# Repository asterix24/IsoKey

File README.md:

# IsoKey
Isometrical keyboard keys

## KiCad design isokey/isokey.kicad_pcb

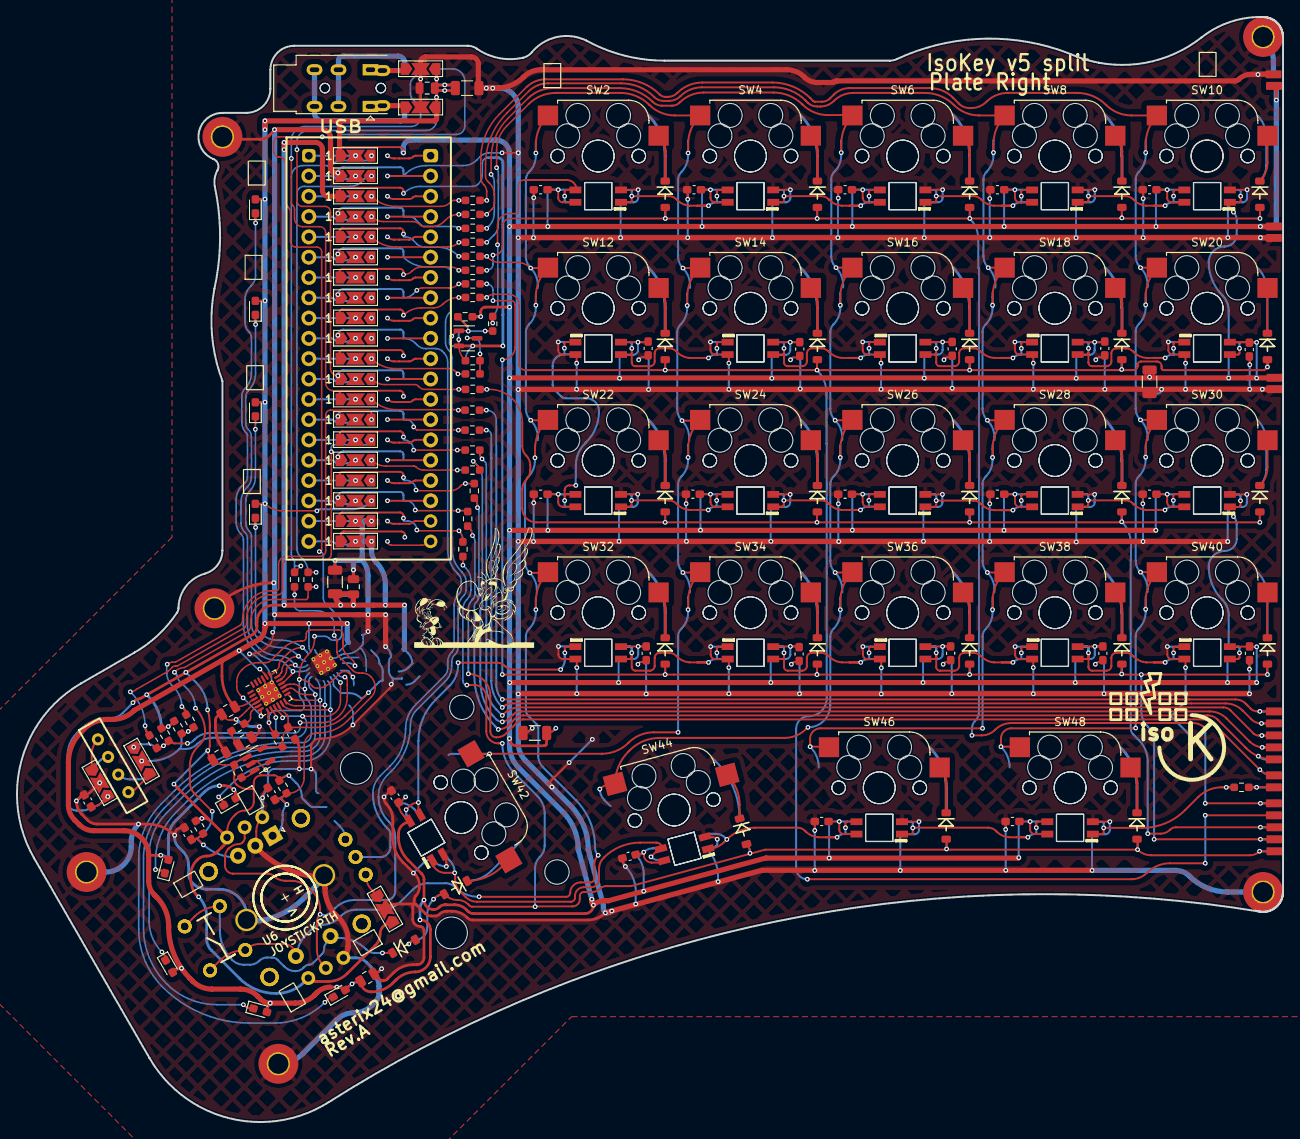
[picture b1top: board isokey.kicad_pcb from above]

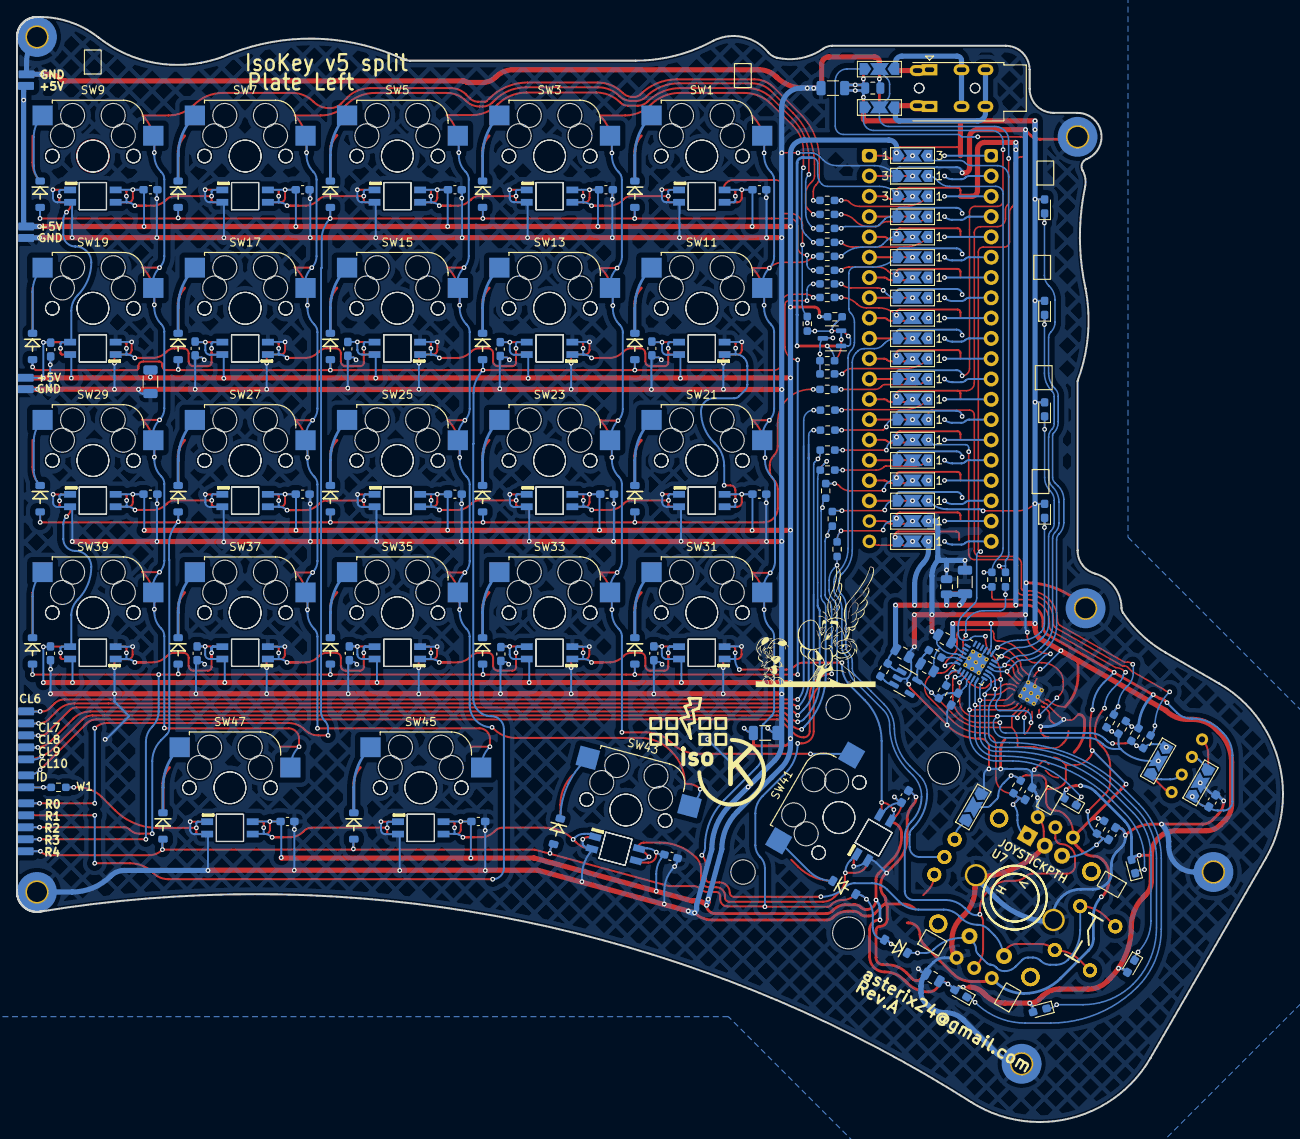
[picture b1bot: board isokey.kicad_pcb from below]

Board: 2 copper layers, 158.4 x 138.3 mm, 392 parts (182 on the bottom side), 200 nets.

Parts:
C1, C3, C10, C11, C38, C64, C71, C73, C74, C75, C87, C89: 1uF; C_0805_2012Metric
C2, C4, C5, C6, C63, C65, C66, C67: 10uF; C_1206_3216Metric
C7, C8, C9, C14, C15, C16, C17, C18, C19, C20, C21, C22, C23, C24, C25, C26, C27, C28, C29, C30, C31, C32, C33, C34, C35, C36, C37, C39, C40, C41, C42, C43, C44, C45, C46, C47, C48, C49, C50, C51, C52, C53, C54, C55, C56, C57, C58, C59, C60, C61, C62, C68, C69, C70, C72, C88: 100nF; C_0603_1608Metric_Pad1.08x0.95mm_HandSolder
D1, D2, D3, D4, D5, D6, D7, D8, D9, D10, D11, D12, D13, D14, D15, D16, D17, D18, D19, D20, D21, D22, D23, D24, D25, D26, D27, D28, D29, D74, D119, D120, D121, D122, D123, D124, D125, D126, D127, D128, D129, D130, D131, D132, D133, D134, D135, D136, D137, D138: 1N4448W; D_SOD-123
D30, D31, D32, D33, D34, D35, D36, D37, D38, D39, D40, D41, D42, D43, D44, D45, D46, D47, D48, D49, D50, D51, D52, D53, D54, D55, D56, D57, D58, D59, D60, D61, D62, D63, D64, D65, D66, D67, D68, D69, D70, D71, D72, D73, D75, D76, D77, D78: SK6812MINI-E; LED_SK6812MINI_PLCC4_3.5x3.5mm_P1.75mm
D79, D80, D81, D82, D83, D84, D85, D86, D87, D110, D111, D112, D113, D114, D115, D116, D117, D118: LED; LED_0603_1608Metric_Pad1.05x0.95mm_HandSolder
H1, H2, H3, H5, H6, H7: MountingHole_Pad; MountingHole_2.5mm_Pad_TopBottom
H4: StabilizerHoles; Stabilizer_MX_2u
J1, J2: PJ-320A-4P; Jack_3.5mm_PJ320E_Horizontal
JP1, JP2, JP3, JP4, JP5, JP6, JP7, JP8, JP9, JP10, JP11, JP12, JP13, JP14, JP15, JP16, JP17, JP18, JP19, JP20, JP21, JP22, JP23, JP24, JP25, JP26, JP27, JP28, JP29, JP30, JP31, JP32, JP33, JP34, JP35, JP36, JP37, JP38, JP39, JP40, JP41, JP42, JP43, JP44, JP45, JP46, JP47, JP48, JP49, JP50: SolderJumper_3_Open_line; SolderJumper-3_P2.0mm_Open_TrianglePad1.0x1.5mm_NumberLabels
Q2, Q3: BSS138; SOT-23-3
R1, R20: 4k7; R_0603_1608Metric_Pad0.98x0.95mm_HandSolder
R2, R4, R5, R6, R7, R8, R9, R10, R11, R12, R13, R15, R17, R19, R21, R23, R25, R27, R28, R29, R30, R31, R32, R33, R34, R35, R42, R43, R44, R48, R49, R50, R51, R52, R53, R54, R55, R56, R57, R58, R59, R60, R61, R62, R63, R64: 22R; R_0603_1608Metric_Pad0.98x0.95mm_HandSolder
R3, R14, R16, R18, R22, R24, R26, R36, R37, R38, R39, R40, R41, R46, R47, R65: 10k; R_0603_1608Metric_Pad0.98x0.95mm_HandSolder
RSW1: RotaryEncoder_Switch; RotaryEncoder_Alps_EC12E-Switch_Vertical_H20mm_CircularMoun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
SW1, SW2, SW3, SW4, SW5, SW6, SW7, SW8, SW9, SW10, SW11, SW12, SW13, SW14, SW15, SW16, SW17, SW18, SW19, SW20, SW21, SW22, SW23, SW24, SW25, SW26, SW27, SW28, SW29, SW30, SW31, SW32, SW33, SW34, SW35, SW36, SW37, SW38, SW39, SW40, SW41, SW42, SW43, SW44, SW45, SW46, SW47, SW48: Cherry; Kailh_socket_MX_LED
TP1: CL6; Testpoint_Pad_1.0x2.0mm
TP2: CL7; Testpoint_Pad_1.0x2.0mm
TP3: CL8; Testpoint_Pad_1.0x2.0mm
TP4: CL9; Testpoint_Pad_1.0x2.0mm
TP5, TP9, TP18: +5V; Testpoint_Pad_1.0x2.0mm
TP6, TP10, TP17: GND; Testpoint_Pad_1.0x2.0mm
TP7: CL10; Testpoint_Pad_1.0x2.0mm
TP8: ID; Testpoint_Pad_1.0x2.0mm
TP11: W1; Testpoint_Pad_1.0x2.0mm
TP12: R0; Testpoint_Pad_1.0x2.0mm
TP13: R1; Testpoint_Pad_1.0x2.0mm
TP14: R2; Testpoint_Pad_1.0x2.0mm
TP15: R3; Testpoint_Pad_1.0x2.0mm
TP16: R4; Testpoint_Pad_1.0x2.0mm
U1: BlackPill_STLINK; BlackPill
U2: OLED_Display_128x32_SSD1306_i2c
U3, U9: TLV73318PDBV; SOT-23-5
U5, U8: WQFN-24-1EP_4x4mm_P0.5mm_EP2.45x2.45mm_ThermalVias
U6, U7: JOYSTICKPTH; JOYSTICK

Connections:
+1V8: C11.1, C72.1, C75.1, C88.1, R24.1, R26.1, R46.1, R47.1, U3.5 (OUT), U5.10 (V1P8), U8.10 (V1P8), U9.5 (OUT)
+3.3V: C1.1, C2.1, C7.1, C10.1, C38.1, C63.1, C70.1, C74.1, JP3.1 (A), JP20.3 (B), JP21.1 (A), JP38.3 (B), JP41.3 (B), JP42.3 (B), JP43.3 (B), JP44.2 (C), Q2.2 (G), Q3.2 (G), R3.2, R14.1, R16.1, R18.2, R22.2, R36.1, R37.1, R38.2, R39.2, R40.2, R41.2, R65.2, U3.1 (IN), U6.V1 (V+), U7.V1 (V+), U9.1 (IN)
+5V: C3.1, C4.1, C5.1, C6.1, C14.1, C15.1, C16.1, C17.1, C18.1, C19.1, C20.1, C21.1, C22.1, C23.1, C24.1, C25.1, C26.1, C27.1, C28.1, C29.1, C30.1, C31.1, C32.1, C33.1, C34.1, C35.1, C36.1, C37.1, C39.1, C40.1, C41.1, C42.1, C43.1, C44.1, C45.1, C46.1, C47.1, C48.1, C49.1, C50.1, C51.1, C52.1, C53.1, C54.1, C55.1, C56.1, C57.1, C58.1, C59.1, C60.1, C61.1, C62.1, C64.1, C65.1, C66.1, C67.1, C71.1, C73.1, C87.1, C89.1, D30.4 (VDD), D31.4 (VDD), D32.4 (VDD), D33.4 (VDD), D34.4 (VDD), D35.4 (VDD), D36.4 (VDD), D37.4 (VDD), D38.4 (VDD), D39.4 (VDD), D40.4 (VDD), D41.4 (VDD), D42.4 (VDD), D43.4 (VDD), D44.4 (VDD), D45.4 (VDD), D46.4 (VDD), D47.4 (VDD), D48.4 (VDD), D49.4 (VDD), D50.4 (VDD), D51.4 (VDD), D52.4 (VDD), D53.4 (VDD), D54.4 (VDD), D55.4 (VDD), D56.4 (VDD), D57.4 (VDD), D58.4 (VDD), D59.4 (VDD), D60.4 (VDD), D61.4 (VDD), D62.4 (VDD), D63.4 (VDD), D64.4 (VDD), D65.4 (VDD), D66.4 (VDD), D67.4 (VDD), D68.4 (VDD), D69.4 (VDD), D70.4 (VDD), D71.4 (VDD), D72.4 (VDD), D73.4 (VDD), D75.4 (VDD), D76.4 (VDD), D77.4 (VDD), D78.4 (VDD), D79.2 (A), D80.2 (A), D81.2 (A), D82.2 (A), D83.2 (A), D84.2 (A), D85.2 (A), D86.2 (A), D87.2 (A), D110.2 (A), D111.2 (A), D112.2 (A), D113.2 (A), D114.2 (A), D115.2 (A), D116.2 (A), D117.2 (A), D118.2 (A), JP2.1 (A), JP18.3 (B), JP23.1 (A), JP40.1 (A), JP49.3 (B), JP50.3 (B), R1.2, R20.2, TP5.1, TP9.1, TP18.1, U5.3 (Vin), U5.20 (ADDR), U8.3 (Vin), U8.20 (ADDR)
/1: JP2.2 (C), U1.1 (PB12)
/2: JP1.2 (C), U1.2 (PB13)
/3: JP3.2 (C), U1.3 (PB14)
/4: JP4.2 (C), U1.4 (PB15)
/5: JP5.2 (C), U1.5 (PA8)
/6: JP6.2 (C), U1.6 (PA9)
/7: JP7.2 (C), U1.7 (PA10)
/8: JP8.2 (C), U1.8 (PA11)
/9: JP9.2 (C), U1.9 (PA12)
/10: JP10.2 (C), U1.10 (PA15)
/11: JP11.2 (C), U1.11 (PB3)
/12: JP12.2 (C), U1.12 (PB4)
/13: JP13.2 (C), U1.13 (PB5)
/14: JP14.2 (C), U1.14 (PB6)
/15: JP15.2 (C), U1.15 (PB7)
/16: JP16.2 (C), U1.16 (PB8)
/17: JP17.2 (C), U1.17 (PB9)
/18: JP18.2 (C), U1.18 (5V)
/19: JP19.2 (C), U1.19 (GND)
/20: JP20.2 (C), U1.20 (3V3)
/21: JP21.2 (C), U1.21 (VBAT)
/22: JP22.2 (C), U1.22 (PC13)
/23: JP23.2 (C), U1.23 (PC14)
/24: JP24.2 (C), U1.24 (PC15)
/25: JP25.2 (C), U1.25 (~RESET)
/26: JP26.2 (C), U1.26 (PA0)
/27: JP27.2 (C), U1.27 (PA1)
/28: JP28.2 (C), U1.28 (PA2)
/29: JP29.2 (C), U1.29 (PA3)
/30: JP30.2 (C), U1.30 (PA4)
/31: JP31.2 (C), U1.31 (PA5)
/32: JP32.2 (C), U1.32 (PA6)
/33: JP33.2 (C), U1.33 (PA7)
/34: JP34.2 (C), U1.34 (PB0)
/35: JP35.2 (C), U1.35 (PB1)
/36: JP36.2 (C), U1.36 (PB2)
/37: JP37.2 (C), U1.37 (PB10)
/38: JP38.2 (C), U1.38 (3V3)
/39: JP39.2 (C), U1.39 (GND)
/40: JP40.2 (C), U1.40 (5V)
/ENC1A: C68.1, C69.1, R40.1, R41.1, R61.1, R62.1, RSW1.A
/ENC1B: C8.1, C9.1, R38.1, R39.1, R63.1, R64.1, RSW1.B
/Interfaces/h1: JP43.1 (A), U6.H1 (H+), U7.H3 (H-)
/Interfaces/h3: JP44.1 (A), U6.H3 (H-), U7.H1 (H+)
/Led_CLK: U5.6 (CLK), U8.6 (CLK)
/Led_INT: JP47.3 (B), R24.2, R46.2, U5.7 (GPIO/TRIG/INT), U8.7 (GPIO/TRIG/INT)
/cl0: R23.1, R25.1, RSW1.S2, SW1.2, SW2.1, SW11.2, SW12.1, SW21.2, SW22.1, SW31.2, SW32.1, U6.B1A (SEL+), U6.B2A (SEL+), U7.B1B (SEL-), U7.B2B (SEL-)
/cl1: R27.1, R29.1, SW3.2, SW4.1, SW13.2, SW14.1, SW23.2, SW24.1, SW33.2, SW34.1, SW41.2, SW42.1
/cl2: R31.1, R32.1, SW5.2, SW6.1, SW15.2, SW16.1, SW25.2, SW26.1, SW35.2, SW36.1, SW43.2, SW44.1
/cl3: R33.1, R34.1, SW7.2, SW8.1, SW17.2, SW18.1, SW27.2, SW28.1, SW37.2, SW38.1, SW45.2, SW46.1
/cl4: R35.1, R43.1, SW9.2, SW10.1, SW19.2, SW20.1, SW29.2, SW30.1, SW39.2, SW40.1, SW47.2, SW48.1
/cl5: R48.1, R49.1, TP1.1
/cl6: R50.1, R51.1, TP2.1
/cl7: R52.1, R53.1, TP3.1
/cl8: R54.1, R55.1, TP4.1
/cl9: R56.1, R57.1, TP7.1
/led_SCL: JP45.2 (C), JP46.2 (C), R14.2, R36.2, R42.1, R58.1, U5.9 (SCL), U8.9 (SCL)
/led_SDA: JP45.3 (B), JP46.3 (B), R16.2, R37.2, R59.1, R60.1, U5.8 (SDA), U8.8 (SDA)
/led_driver/l0: D80.1 (K), D111.1 (K), U5.19 (LED0), U8.19 (LED0)
/led_driver/l1: D81.1 (K), D112.1 (K), U5.18 (LED1), U8.18 (LED1)
/led_driver/l2: D82.1 (K), D113.1 (K), U5.17 (LED2), U8.17 (LED2)
/led_driver/l3: D83.1 (K), D114.1 (K), U5.16 (LED3), U8.16 (LED3)
/led_driver/l4: D84.1 (K), D115.1 (K), U5.15 (LED4), U8.15 (LED4)
/led_driver/l5: D85.1 (K), D116.1 (K), U5.14 (LED5), U8.14 (LED5)
/led_driver/l6: D86.1 (K), D117.1 (K), U5.13 (LED6), U8.13 (LED6)
/led_driver/l7: D87.1 (K), D118.1 (K), U5.12 (LED7), U8.12 (LED7)
/led_driver/l8: D79.1 (K), D110.1 (K), U5.11 (LED8), U8.11 (LED8)
/led_w1: Q2.3 (S), Q3.3 (S), R3.1, R6.1, R22.1, R30.1
/led_w1_in: Q2.1 (D), Q3.1 (D), R1.1, R20.1, R28.1, R44.1
/led_w1_out: D73.1 (DOUT), D78.1 (DOUT), R8.2, R12.2
/pa0: JP15.1 (A), JP26.3 (B), R52.2, R53.2
/pa1: JP14.1 (A), JP27.3 (B), R50.2, R51.2
/pa2: JP13.1 (A), JP28.3 (B), JP47.2 (C), JP48.2 (C)
/pa3: JP12.1 (A), JP29.3 (B), JP48.3 (B)
/pa4: JP11.1 (A), JP30.3 (B)
/pa5: JP10.1 (A), JP31.3 (B), U6.H2 (H), U7.H2 (H)
/pa6: JP9.1 (A), JP32.3 (B), R5.2, R7.2
/pa7: JP8.1 (A), JP33.3 (B), R15.2, R17.2
/pa8: JP5.3 (B), JP36.1 (A), R27.2, R29.2
/pa9: JP6.3 (B), JP35.1 (A)
/pa10: JP7.3 (B), JP34.1 (A)
/pa11: JP8.3 (B), JP33.1 (A)
/pa12: JP9.3 (B), JP32.1 (A)
/pa15: JP10.3 (B), JP31.1 (A)
/pb0: JP7.1 (A), JP34.3 (B), R2.2, R4.2
/pb1: JP6.1 (A), JP35.3 (B), U6.V2 (V), U7.V2 (V)
/pb2: JP5.1 (A), JP36.3 (B), R23.2, R25.2
/pb3: JP11.3 (B), JP30.1 (A), R6.2, R30.2
/pb4: JP12.3 (B), JP29.1 (A), R9.2, R13.2
/pb5: JP13.3 (B), JP28.1 (A), R48.2, R49.2
/pb6: JP14.3 (B), JP27.1 (A), R42.2, R58.2
/pb7: JP15.3 (B), JP26.1 (A), R59.2, R60.2
/pb8: JP16.3 (B), JP25.1 (A), R54.2, R55.2
/pb9: JP17.3 (B), JP24.1 (A)
/pb10: JP4.1 (A), JP37.3 (B), R31.2, R32.2
/pb12: JP2.3 (B), JP40.3 (B), R61.2, R62.2
/pb13: JP1.3 (B), JP39.1 (A), R63.2, R64.2
/pb14: JP3.3 (B), JP38.1 (A), R35.2, R43.2
/pb15: JP4.3 (B), JP37.1 (A), R33.2, R34.2
/pc13: JP19.1 (A), JP22.3 (B), R19.2, R21.2
/pc14: JP18.1 (A), JP23.3 (B), R10.2, R11.2
/pc15: JP17.1 (A), JP24.3 (B), R56.2, R57.2
/r0: D1.2 (A), D2.2 (A), D3.2 (A), D4.2 (A), D5.2 (A), D6.2 (A), D7.2 (A), D8.2 (A), D9.2 (A), D10.2 (A), R2.1, R4.1, TP12.1
/r1: D11.2 (A), D12.2 (A), D13.2 (A), D14.2 (A), D15.2 (A), D16.2 (A), D17.2 (A), D18.2 (A), D19.2 (A), D20.2 (A), R5.1, R7.1, TP13.1
/r2: D21.2 (A), D22.2 (A), D23.2 (A), D24.2 (A), D26.2 (A), D27.2 (A), D28.2 (A), D29.2 (A), D119.2 (A), D120.2 (A), R9.1, R13.1, TP14.1
/r3: D121.2 (A), D122.2 (A), D123.2 (A), D124.2 (A), D125.2 (A), D126.2 (A), D127.2 (A), D128.2 (A), D129.2 (A), D130.2 (A), R15.1, R17.1, TP15.1
/r4: D25.2 (A), D74.2 (A), D131.2 (A), D132.2 (A), D133.2 (A), D134.2 (A), D135.2 (A), D136.2 (A), D137.2 (A), D138.2 (A), R19.1, R21.1, TP16.1
/reset: JP16.1 (A), JP25.3 (B)
/sw0_r: D25.1 (K), D74.1 (K), RSW1.S1, U6.B1B (SEL-), U6.B2B (SEL-), U7.B1A (SEL+), U7.B2A (SEL+)
GND: C1.2, C2.2, C3.2, C4.2, C5.2, C6.2, C7.2, C8.2, C9.2, C10.2, C11.2, C14.2, C15.2, C16.2, C17.2, C18.2, C19.2, C20.2, C21.2, C22.2, C23.2, C24.2, C25.2, C26.2, C27.2, C28.2, C29.2, C30.2, C31.2, C32.2, C33.2, C34.2, C35.2, C36.2, C37.2, C38.2, C39.2, C40.2, C41.2, C42.2, C43.2, C44.2, C45.2, C46.2, C47.2, C48.2, C49.2, C50.2, C51.2, C52.2, C53.2, C54.2, C55.2, C56.2, C57.2, C58.2, C59.2, C60.2, C61.2, C62.2, C63.2, C64.2, C65.2, C66.2, C67.2, C68.2, C69.2, C70.2, C71.2, C72.2, C73.2, C74.2, C75.2, C87.2, C88.2, C89.2, D30.2 (VSS), D31.2 (VSS), D32.2 (VSS), D33.2 (VSS), D34.2 (VSS), D35.2 (VSS), D36.2 (VSS), D37.2 (VSS), D38.2 (VSS), D39.2 (VSS), D40.2 (VSS), D41.2 (VSS), D42.2 (VSS), D43.2 (VSS), D44.2 (VSS), D45.2 (VSS), D46.2 (VSS), D47.2 (VSS), D48.2 (VSS), D49.2 (VSS), D50.2 (VSS), D51.2 (VSS), D52.2 (VSS), D53.2 (VSS), D54.2 (VSS), D55.2 (VSS), D56.2 (VSS), D57.2 (VSS), D58.2 (VSS), D59.2 (VSS), D60.2 (VSS), D61.2 (VSS), D62.2 (VSS), D63.2 (VSS), D64.2 (VSS), D65.2 (VSS), D66.2 (VSS), D67.2 (VSS), D68.2 (VSS), D69.2 (VSS), D70.2 (VSS), D71.2 (VSS), D72.2 (VSS), D73.2 (VSS), D75.2 (VSS), D76.2 (VSS), D77.2 (VSS), D78.2 (VSS), H1.1, H2.1, H3.1, H5.1, H6.1, H7.1, JP1.1 (A), JP19.3 (B), JP22.1 (A), JP39.3 (B), JP41.2 (C), JP42.2 (C), JP43.2 (C), JP44.3 (B), JP49.2 (C), JP50.2 (C), RSW1.C, RSW1.MP, TP6.1, TP10.1, TP17.1, U3.2 (GND), U5.4 (AGND), U5.21 (PGND), U5.25 (GND_PAD), U6.V3 (V-), U7.V3 (V-), U8.4 (AGND), U8.21 (PGND), U8.25 (GND_PAD), U9.2 (GND)
unnamed: D1.1 (K), SW1.1
unnamed: D2.1 (K), SW2.2
unnamed: D3.1 (K), SW3.1
unnamed: D4.1 (K), SW4.2
unnamed: D5.1 (K), SW5.1
unnamed: D6.1 (K), SW6.2
unnamed: D7.1 (K), SW7.1
unnamed: D8.1 (K), SW8.2
unnamed: D9.1 (K), SW9.1
unnamed: D10.1 (K), SW10.2
unnamed: D11.1 (K), SW11.1
unnamed: D12.1 (K), SW12.2
unnamed: D13.1 (K), SW13.1
unnamed: D14.1 (K), SW14.2
unnamed: D15.1 (K), SW15.1
unnamed: D16.1 (K), SW16.2
unnamed: D17.1 (K), SW17.1
unnamed: D18.1 (K), SW18.2
unnamed: D19.1 (K), SW19.1
unnamed: D20.1 (K), SW20.2
unnamed: D21.1 (K), SW21.1
unnamed: D22.1 (K), SW22.2
unnamed: D23.1 (K), SW23.1
unnamed: D24.1 (K), SW24.2
unnamed: D26.1 (K), SW25.1
unnamed: D27.1 (K), SW26.2
unnamed: D28.1 (K), SW27.1
unnamed: D29.1 (K), SW28.2
unnamed: D30.3 (DIN), D31.3 (DIN), R28.2, R44.2
unnamed: D30.1 (DOUT), D31.1 (DOUT), D32.3 (DIN), D33.3 (DIN)
unnamed: D32.1 (DOUT), D33.1 (DOUT), D34.3 (DIN), D35.3 (DIN)
unnamed: D34.1 (DOUT), D35.1 (DOUT), D36.3 (DIN), D37.3 (DIN)
unnamed: D36.1 (DOUT), D37.1 (DOUT), D38.3 (DIN), D39.3 (DIN)
unnamed: D38.1 (DOUT), D39.1 (DOUT), D40.3 (DIN), D45.3 (DIN)
unnamed: D40.1 (DOUT), D41.3 (DIN), D45.1 (DOUT), D46.3 (DIN)
unnamed: D41.1 (DOUT), D42.3 (DIN), D46.1 (DOUT), D47.3 (DIN)
unnamed: D42.1 (DOUT), D43.3 (DIN), D47.1 (DOUT), D48.3 (DIN)
unnamed: D43.1 (DOUT), D44.3 (DIN), D48.1 (DOUT), D49.3 (DIN)
unnamed: D44.1 (DOUT), D49.1 (DOUT), D50.3 (DIN), D55.3 (DIN)
unnamed: D50.1 (DOUT), D51.3 (DIN), D55.1 (DOUT), D56.3 (DIN)
unnamed: D51.1 (DOUT), D52.3 (DIN), D56.1 (DOUT), D57.3 (DIN)
unnamed: D52.1 (DOUT), D53.3 (DIN), D57.1 (DOUT), D58.3 (DIN)
unnamed: D53.1 (DOUT), D54.3 (DIN), D58.1 (DOUT), D59.3 (DIN)
unnamed: D54.1 (DOUT), D59.1 (DOUT), D60.3 (DIN), D65.3 (DIN)
unnamed: D60.1 (DOUT), D61.3 (DIN), D65.1 (DOUT), D66.3 (DIN)
unnamed: D61.1 (DOUT), D62.3 (DIN), D66.1 (DOUT), D67.3 (DIN)
unnamed: D62.1 (DOUT), D63.3 (DIN), D67.1 (DOUT), D68.3 (DIN)
unnamed: D63.1 (DOUT), D64.3 (DIN), D68.1 (DOUT), D69.3 (DIN)
unnamed: D64.1 (DOUT), D69.1 (DOUT), D70.3 (DIN), D75.3 (DIN)
unnamed: D70.1 (DOUT), D71.3 (DIN), D75.1 (DOUT), D76.3 (DIN)
unnamed: D71.1 (DOUT), D72.3 (DIN), D76.1 (DOUT), D77.3 (DIN)
unnamed: D72.1 (DOUT), D73.3 (DIN), D77.1 (DOUT), D78.3 (DIN)
unnamed: D119.1 (K), SW29.1
unnamed: D120.1 (K), SW30.2
unnamed: D121.1 (K), SW31.1
unnamed: D122.1 (K), SW32.2
unnamed: D123.1 (K), SW33.1
unnamed: D124.1 (K), SW34.2
unnamed: D125.1 (K), SW35.1
unnamed: D126.1 (K), SW36.2
unnamed: D127.1 (K), SW37.1
unnamed: D128.1 (K), SW38.2
unnamed: D129.1 (K), SW39.1
unnamed: D130.1 (K), SW40.2
unnamed: D131.1 (K), SW41.1
unnamed: D132.1 (K), SW42.2
unnamed: D133.1 (K), SW43.1
unnamed: D134.1 (K), SW44.2
unnamed: D135.1 (K), SW45.1
unnamed: D136.1 (K), SW46.2
unnamed: D137.1 (K), SW47.1
unnamed: D138.1 (K), SW48.2
unnamed: JP41.1 (A), U2.2 (Vcc)
unnamed: JP42.1 (A), U2.1 (GND)
unnamed: JP45.1 (A), U2.3 (SCL)
unnamed: JP46.1 (A), U2.4 (SDA)
unnamed: J1.R1, J2.R1, JP47.1 (A)
unnamed: J1.R2, J2.R2, JP48.1 (A)
unnamed: J1.S, J2.T, JP49.1 (A)
unnamed: J1.T, J2.S, JP50.1 (A)
unnamed: R10.1, R11.1, TP8.1
unnamed: R8.1, R12.1, TP11.1
unnamed: R18.1, U3.3 (EN)
unnamed: R47.2, U5.5 (EN/PWM)
unnamed: R26.2, U8.5 (EN/PWM)
unnamed: R65.1, U9.3 (EN)
V_BATT: JP20.1 (A), JP21.3 (B)

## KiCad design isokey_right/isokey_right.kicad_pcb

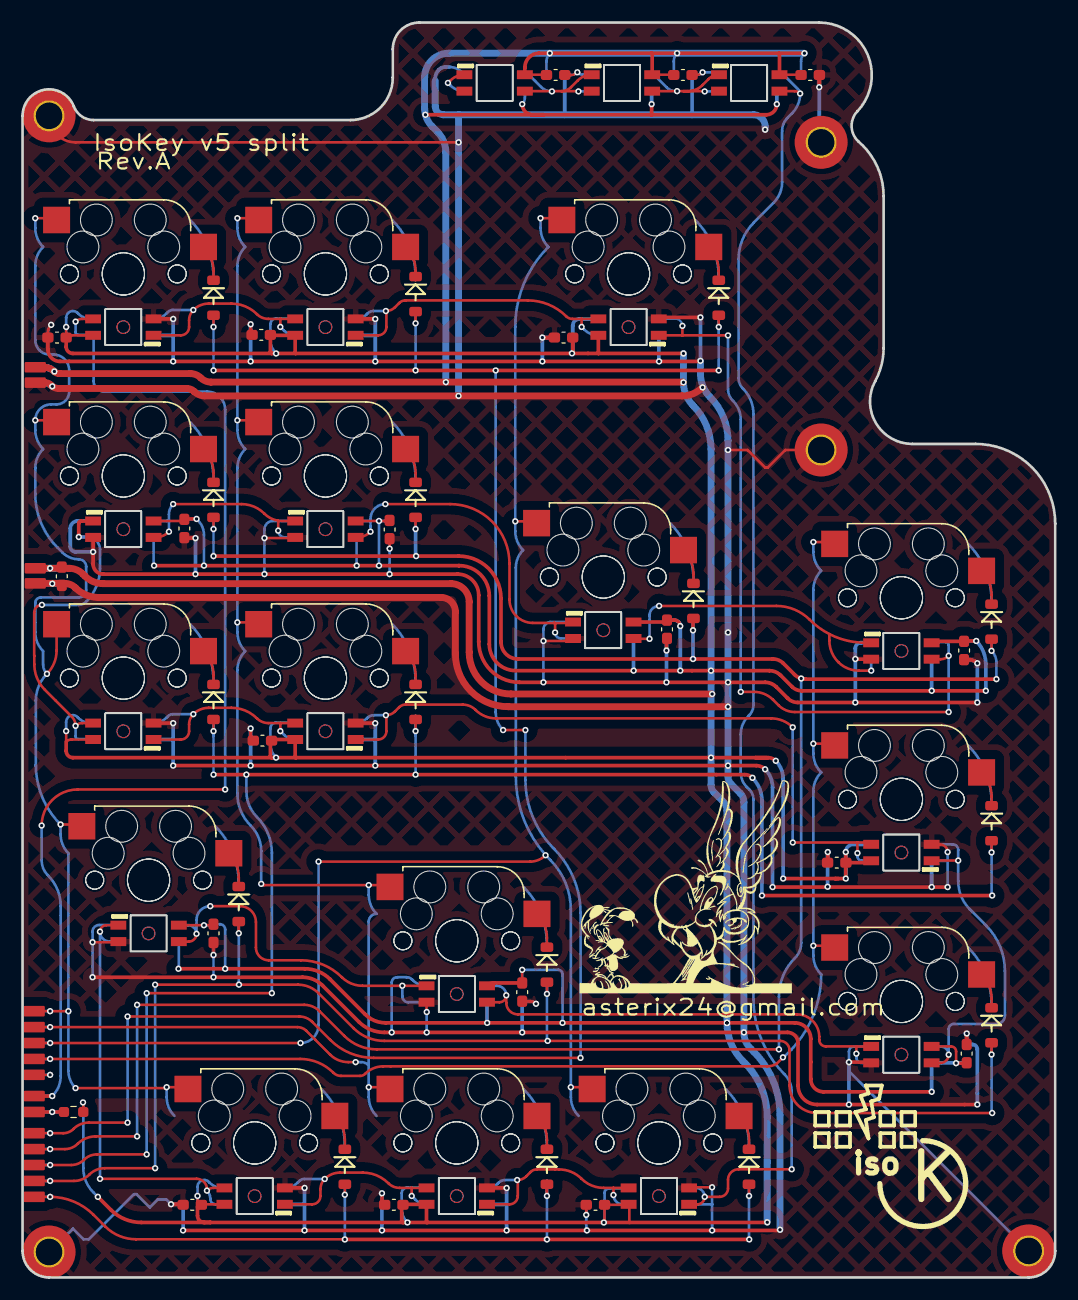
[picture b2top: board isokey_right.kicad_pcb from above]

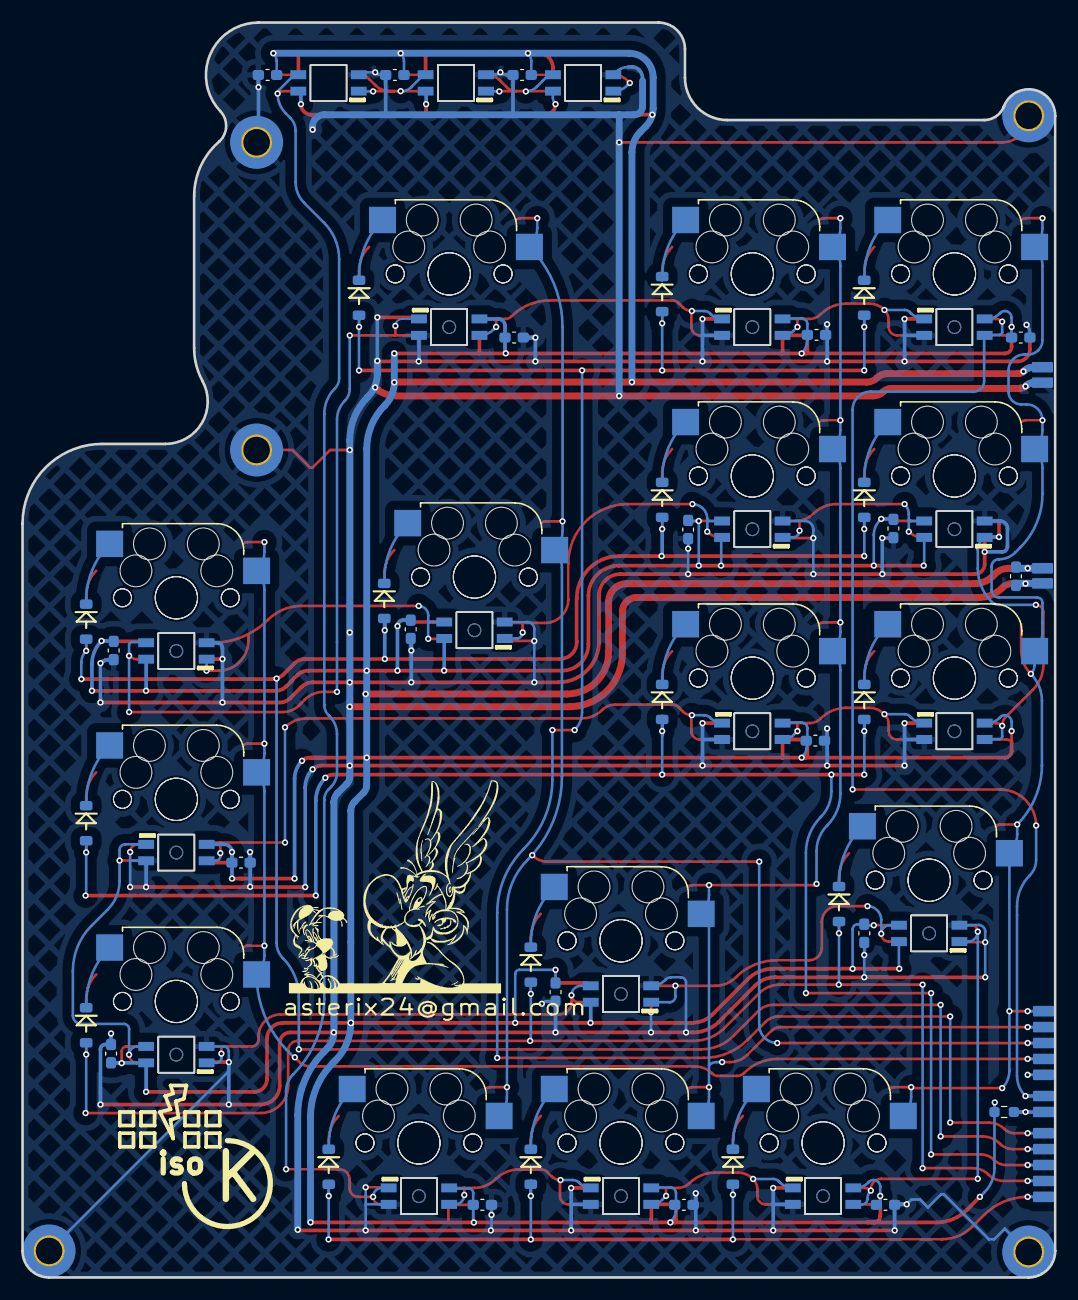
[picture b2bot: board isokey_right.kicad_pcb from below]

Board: 2 copper layers, 97.3 x 118.3 mm, 163 parts (71 on the bottom side), 64 nets.

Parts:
C1, C2, C3, C4, C5, C6, C7, C8, C9, C10, C11, C12, C13, C14, C15, C16, C17, C18, C19, C20, C21, C22, C23, C24, C25, C26, C27, C28, C29, C30, C31, C32, C33, C34, C35, C36, C37, C38: 100nF; C_0603_1608Metric_Pad1.08x0.95mm_HandSolder
D1, D2, D3, D4, D5, D6, D9, D10, D11, D12, D13, D14, D15, D16, D17, D18, D21, D22, D23, D24, D27, D28, D31, D32, D33, D34, D37, D38, D43, D44, D45, D46: 1N4448W; D_SOD-123
D7, D8, D19, D20, D25, D26, D29, D30, D35, D36, D39, D40, D41, D42, D47, D48, D49, D50, D51, D52, D53, D54, D55, D56, D57, D58, D59, D60, D61, D62, D63, D64, D65, D66, D67, D68, D69, D70: SK6812MINI-E; LED_SK6812MINI_PLCC4_3.5x3.5mm_P1.75mm
H1, H2, H3, H4, H5: MountingHole_Pad; MountingHole_2.5mm_Pad_TopBottom
R3, R4: 10k; R_0603_1608Metric_Pad0.98x0.95mm_HandSolder
SW1, SW2, SW3, SW4, SW5, SW6, SW9, SW10, SW11, SW12, SW13, SW14, SW15, SW16, SW17, SW18, SW21, SW22, SW23, SW24, SW27, SW28, SW31, SW32, SW33, SW34, SW37, SW38, SW41, SW42, SW43, SW44: Cherry; Kailh_socket_MX_LED
TP1: W1; Testpoint_Pad_1.0x2.0mm
TP2: ID; Testpoint_Pad_1.0x2.0mm
TP3, TP4: +5V; Testpoint_Pad_1.0x2.0mm
TP5: CL6; Testpoint_Pad_1.0x2.0mm
TP6: CL7; Testpoint_Pad_1.0x2.0mm
TP7: CL8; Testpoint_Pad_1.0x2.0mm
TP8: CL9; Testpoint_Pad_1.0x2.0mm
TP9: CL10; Testpoint_Pad_1.0x2.0mm
TP10: R0; Testpoint_Pad_1.0x2.0mm
TP11: R1; Testpoint_Pad_1.0x2.0mm
TP12: R2; Testpoint_Pad_1.0x2.0mm
TP13: R3; Testpoint_Pad_1.0x2.0mm
TP14: R4; Testpoint_Pad_1.0x2.0mm
TP15, TP16: GND; Testpoint_Pad_1.0x2.0mm

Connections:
+5V: C1.1, C2.1, C3.1, C4.1, C5.1, C6.1, C7.1, C8.1, C9.1, C10.1, C11.1, C12.1, C13.1, C14.1, C15.1, C16.1, C17.1, C18.1, C19.1, C20.1, C21.1, C22.1, C23.1, C24.1, C25.1, C26.1, C27.1, C28.1, C29.1, C30.1, C31.1, C32.1, C33.1, C34.1, C35.1, C36.1, C37.1, C38.1, D7.4 (VDD), D8.4 (VDD), D19.4 (VDD), D20.4 (VDD), D25.4 (VDD), D26.4 (VDD), D29.4 (VDD), D30.4 (VDD), D35.4 (VDD), D36.4 (VDD), D39.4 (VDD), D40.4 (VDD), D41.4 (VDD), D42.4 (VDD), D47.4 (VDD), D48.4 (VDD), D49.4 (VDD), D50.4 (VDD), D51.4 (VDD), D52.4 (VDD), D53.4 (VDD), D54.4 (VDD), D55.4 (VDD), D56.4 (VDD), D57.4 (VDD), D58.4 (VDD), D59.4 (VDD), D60.4 (VDD), D61.4 (VDD), D62.4 (VDD), D63.4 (VDD), D64.4 (VDD), D65.4 (VDD), D66.4 (VDD), D67.4 (VDD), D68.4 (VDD), D69.4 (VDD), D70.4 (VDD), R3.2, R4.2, TP3.1, TP4.1
/cl5: SW1.2, SW2.1, SW9.2, SW10.1, SW11.2, SW12.1, SW21.2, SW22.1, SW31.2, SW32.1, TP5.1
/cl6: SW3.2, SW4.1, SW13.2, SW14.1, SW23.2, SW24.1, SW33.2, SW34.1, SW41.2, SW42.1, TP6.1
/cl7: SW5.2, SW6.1, SW15.2, SW16.1, SW43.2, SW44.1, TP7.1
/cl8: SW17.2, SW18.1, SW27.2, SW28.1, SW37.2, SW38.1, TP8.1
/led_plate/led_out: D69.1 (DOUT), D70.1 (DOUT)
/led_w1_out: D7.3 (DIN), D26.3 (DIN), TP1.1
/r0: D1.2 (A), D2.2 (A), D3.2 (A), D4.2 (A), D5.2 (A), D6.2 (A), TP10.1
/r1: D11.2 (A), D12.2 (A), D13.2 (A), D14.2 (A), D15.2 (A), D16.2 (A), D17.2 (A), D18.2 (A), TP11.1
/r2: D21.2 (A), D22.2 (A), D23.2 (A), D24.2 (A), D27.2 (A), D28.2 (A), TP12.1
/r3: D31.2 (A), D32.2 (A), D33.2 (A), D34.2 (A), D37.2 (A), D38.2 (A), TP13.1
/r4: D9.2 (A), D10.2 (A), D43.2 (A), D44.2 (A), D45.2 (A), D46.2 (A), TP14.1
GND: C1.2, C2.2, C3.2, C4.2, C5.2, C6.2, C7.2, C8.2, C9.2, C10.2, C11.2, C12.2, C13.2, C14.2, C15.2, C16.2, C17.2, C18.2, C19.2, C20.2, C21.2, C22.2, C23.2, C24.2, C25.2, C26.2, C27.2, C28.2, C29.2, C30.2, C31.2, C32.2, C33.2, C34.2, C35.2, C36.2, C37.2, C38.2, D7.2 (VSS), D8.2 (VSS), D19.2 (VSS), D20.2 (VSS), D25.2 (VSS), D26.2 (VSS), D29.2 (VSS), D30.2 (VSS), D35.2 (VSS), D36.2 (VSS), D39.2 (VSS), D40.2 (VSS), D41.2 (VSS), D42.2 (VSS), D47.2 (VSS), D48.2 (VSS), D49.2 (VSS), D50.2 (VSS), D51.2 (VSS), D52.2 (VSS), D53.2 (VSS), D54.2 (VSS), D55.2 (VSS), D56.2 (VSS), D57.2 (VSS), D58.2 (VSS), D59.2 (VSS), D60.2 (VSS), D61.2 (VSS), D62.2 (VSS), D63.2 (VSS), D64.2 (VSS), D66.2 (VSS), D68.2 (VSS), D69.2 (VSS), H1.1, H2.1, H3.1, H4.1, H5.1, TP15.1, TP16.1
unnamed: D1.1 (K), SW1.1
unnamed: D2.1 (K), SW2.2
unnamed: D3.1 (K), SW3.1
unnamed: D4.1 (K), SW4.2
unnamed: D5.1 (K), SW5.1
unnamed: D6.1 (K), SW6.2
unnamed: D9.1 (K), SW9.1
unnamed: D10.1 (K), SW10.2
unnamed: D11.1 (K), SW11.1
unnamed: D12.1 (K), SW12.2
unnamed: D13.1 (K), SW13.1
unnamed: D14.1 (K), SW14.2
unnamed: D15.1 (K), SW15.1
unnamed: D16.1 (K), SW16.2
unnamed: D17.1 (K), SW17.1
unnamed: D18.1 (K), SW18.2
unnamed: D8.1 (DOUT), D19.3 (DIN), D29.1 (DOUT), D30.3 (DIN)
unnamed: D19.1 (DOUT), D20.3 (DIN), D30.1 (DOUT), D35.3 (DIN)
unnamed: D20.1 (DOUT), D25.3 (DIN), D35.1 (DOUT), D36.3 (DIN)
unnamed: D21.1 (K), SW21.1
unnamed: D22.1 (K), SW22.2
unnamed: D23.1 (K), SW23.1
unnamed: D24.1 (K), SW24.2
unnamed: D25.1 (DOUT), D36.1 (DOUT), D39.3 (DIN), D48.3 (DIN)
unnamed: D7.1 (DOUT), D8.3 (DIN), D26.1 (DOUT), D29.3 (DIN)
unnamed: D27.1 (K), SW27.1
unnamed: D28.1 (K), SW28.2
unnamed: D31.1 (K), SW31.1
unnamed: D32.1 (K), SW32.2
unnamed: D33.1 (K), SW33.1
unnamed: D34.1 (K), SW34.2
unnamed: D37.1 (K), SW37.1
unnamed: D38.1 (K), SW38.2
unnamed: D39.1 (DOUT), D40.3 (DIN), D48.1 (DOUT), D49.3 (DIN)
unnamed: D40.1 (DOUT), D41.3 (DIN), D49.1 (DOUT), D50.3 (DIN)
unnamed: D41.1 (DOUT), D42.3 (DIN), D50.1 (DOUT), D51.3 (DIN)
unnamed: D42.1 (DOUT), D47.3 (DIN), D51.1 (DOUT), D52.3 (DIN)
unnamed: D43.1 (K), SW41.1
unnamed: D44.1 (K), SW42.2
unnamed: D45.1 (K), SW43.1
unnamed: D46.1 (K), SW44.2
unnamed: D47.1 (DOUT), D52.1 (DOUT), D53.3 (DIN), D58.3 (DIN)
unnamed: D53.1 (DOUT), D54.3 (DIN), D58.1 (DOUT), D59.3 (DIN)
unnamed: D54.1 (DOUT), D55.3 (DIN), D59.1 (DOUT), D60.3 (DIN)
unnamed: D55.1 (DOUT), D56.3 (DIN), D60.1 (DOUT), D61.3 (DIN)
unnamed: D56.1 (DOUT), D57.3 (DIN), D61.1 (DOUT), D62.3 (DIN)
unnamed: D57.1 (DOUT), D62.1 (DOUT), D63.3 (DIN), D68.3 (DIN)
unnamed: D63.1 (DOUT), D64.3 (DIN), D65.3 (DIN), D68.1 (DOUT)
unnamed: D64.1 (DOUT), D65.1 (DOUT), D66.3 (DIN), D67.3 (DIN)
unnamed: D66.1 (DOUT), D67.1 (DOUT), D69.3 (DIN), D70.3 (DIN)
unnamed: R3.1, R4.1, TP2.1

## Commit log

2023-08-16 Add leds and extra connectors
2023-08-18 Add 3d models
2023-08-20 Add shit template
2023-08-21 Place all sw
2023-08-30 Place switch and leds
2023-08-31 Continue routing
2023-09-03 Complete led wire
2023-09-05 Update blackpill footprint
2023-10-04 Add lp5569 chip and encoder.
2023-10-08 Update scheme. Continue routing.
2023-10-08 Add import layers
2023-12-08 Complete routing
2023-12-10 update outline
2023-12-10 Move left con
2023-12-10 Other layout drawings
2023-12-22 Fix for output file
2023-12-22 Generate output files
2023-12-23 Add trackball scheme
2023-12-30 add ir sensor for trackball
2024-01-12 Add trackball routing
2024-01-24 isokey: start splitting
2024-01-24 dxf of split keyboard
2024-02-10 add dxf of layout
2024-02-11 move oled
2024-03-20 Run dcr
2024-04-14 Reoder prj. Complete routing fix drc.
2024-04-14 Generate ouput files rev.a
2024-04-14 reorder directory
2024-04-14 add board outline
2024-04-21 add v5 dxf profile
2024-04-21 add frame pcb
2024-12-04 Generate gerbers
2024-12-04 Review drawing for new layout
2024-12-05 clean up
2025-03-01 re-align prj
2025-08-03 Add output job files
2025-08-03 Clean up and reorder drawing folder
2025-08-03 Remove unnedded prj
2025-08-03 Complete routing clean up and rename projects
2025-10-29 Update schematics
2025-11-07 Remove led cover part
